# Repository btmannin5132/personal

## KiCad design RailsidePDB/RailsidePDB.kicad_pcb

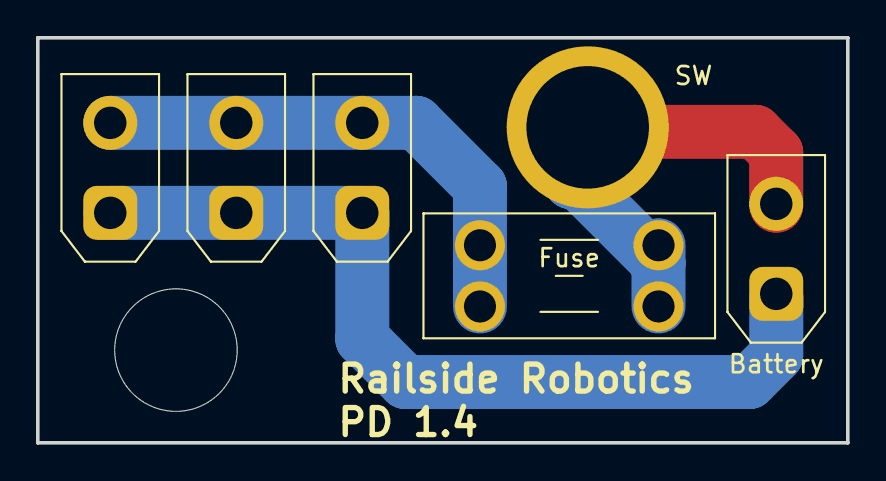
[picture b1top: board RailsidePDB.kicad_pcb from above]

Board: 2 copper layers, 45.0 x 22.5 mm, 5 parts (0 on the bottom side), 2 nets.

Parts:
BT1, BT2, BT3, BT4: Battery; AMASS_XT30UPB-M_1x02_P5.0mm_Vertical
Fuse: Fuse; Fuseholder_Blade_Mini_Keystone_3568

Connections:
unnamed: BT1.1 (+), BT2.1 (+), BT3.1 (+), BT4.1 (+)
unnamed: BT1.2 (-), BT2.2 (-), BT3.2 (-), Fuse.1

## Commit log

2021-09-14 Add Roulette Files
2021-09-14 made greedy comments
2021-09-14 Analyze net gains/loss and max gains and loss
2021-09-14 Looking at average gain/loss per trial
2021-09-14 Moved 3s to function to iterate over many incs
2021-09-14 moved 3s to function
2021-09-14 updated graphing
2021-09-15 Made Roulette Folder
2021-09-15 remove copies
2021-11-05 update on personal projects
2022-03-18 adding
2024-09-25 Add OpenMv
2024-10-16 Add Arduino
2024-10-21 Add Trio for Skulls
2024-10-22 Add new version of singe skull audio filtering
2024-11-21 add skullTrio and RRPDB
2024-12-04 add V3
2025-01-28 Add cribbage pcb and railside vip area
2025-03-05 Add db for PHD information
2025-03-05 add work, education, and achievements
2025-03-05 add concentration to edu.
2025-06-02 sync up pesonal git
2025-08-07 Adding webapp for Arduino R4 Wifi
